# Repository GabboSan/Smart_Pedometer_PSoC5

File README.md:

# AY2022 I Project-1

Smart Pedometer project developed in a MSc Course of Politecnico di Milano:
Authors: 
1. Santicchi Gabriele
2. d'Arenzo Daniele 
3. Santini Matteo

In this work a PSoC CY8C5888LTI-LP097 communicates by I2C protocol with MPU9250, SSD1306, 24LC512 and by UART protocol with HC-06 Bluetooth.\
A PyQt5 GUI has been developed to upload sessions and set user credential.

## Aim of this Work

1. Implement a pedometer algorithm capable to identify and count steps online;
2. Exploit the over-threshold events interrupt of the MPU9250 to automatically wake up the device from sleep; go to sleep mode when no motion is detected for 1 minute;
3. Display in the GUI some statistics: total number of steps, average cadence, total activity time and the session path with respect to the origin (i.e. first 'step' detected);
4. Log the statistics of each session (i.e., of every walk detected) in the internal EEPROM of the PSoC;
5. Minimization of power consumption, by using powersaving functionalities of the PSoC (e.g., Alternate mode) as well as turining off external peripherals when not in use;
6. When connected via USB to the computer, the device can accept a data request and display/send the data stored into the EEPROM.

## MPU9250 and AHRS filtering

To keep track of the direction of the walk, the AHRS filter has been implemented to get a Roll-Pitch-Yaw estimate. As the filter needs the magnetometer measurements, the AK8963 is enabled and set as Slave on the I2C bus.
Each 2 seconds the pedometer algorithm compute the X and Y direction of the walk, by considering the RPY orientation of the device.
The two directions are saved as 16 bit and then saved into the cell of the EEPROM . Path is reconstructed by the PC through this relative coordinates system.

## EEPROM Session Data Structure

When no motion has been detected for 1 minute, the Wake-On-Motion (WOM) interrupt is enabled and session data are saved in the EEPROM with the following structure.\
**RESERVED CELL REGISTERS:**
* 0: Height;
* 1: UserID;
* 2: SessionID;
* 3-4: lastAddressEEPROM: to avoid data overwriting;

**CELL REGISTERS:**

From 24LC512 Datasheet, Read and Write max. operation number is limited to a Page size, which consist of 128 bytes. The Packets to be sent to the PC are structured as:

* UserID, SessionID, HEADER (0xFE,0xFF);
* dataXY: sequence of X and Y relative coordinates (in 16 bits) computed each 2 seconds;
* Number of Steps, TAIL (0xFF,0xFF);

## SSD1306 Display

The SSD1306 communicates by I2C with the Master. It displays the total step counter and the current speed (in cm/s) each 2 seconds. When the device enters in Sleep mode, the display is turned off.

## Final PCB ad Case

# Guide

## Device Guide

Device must be put parallel to the calf fibers in order to get meaningful information about the orientation. During a Session, the Step counter and the Current speed are updated each 2 seconds on the SSD1306 display.\
A session starts when the device is powered, and ends when no motion has been detected for more than 1 minute. Then, the session is saved into the memory and the device enter in sleep mode until detection of futher N steps.

## GUI Guide

While running the GUI, the Device must be connected either by USB or Bluetooth. Even if an automatic scan of ports is implemented, sometimes a manual selection of the COM is required.
To get meaningful information about the orientation, the calibration of the magnetometer is recommended (move the device along an eigth figure until the calibration is not finished).\
The GUI is organized in tabs:

* Sessions: see the statistics related to each session downloaded from the device;
* Live Viewer: see the Session path and the current 3D orientation of the device;
* Edit Profile: to create, delete and modify a user;
* Advanced Tool: monitor Accelerometer, Gyroscope and Magnetometer values in real-time.

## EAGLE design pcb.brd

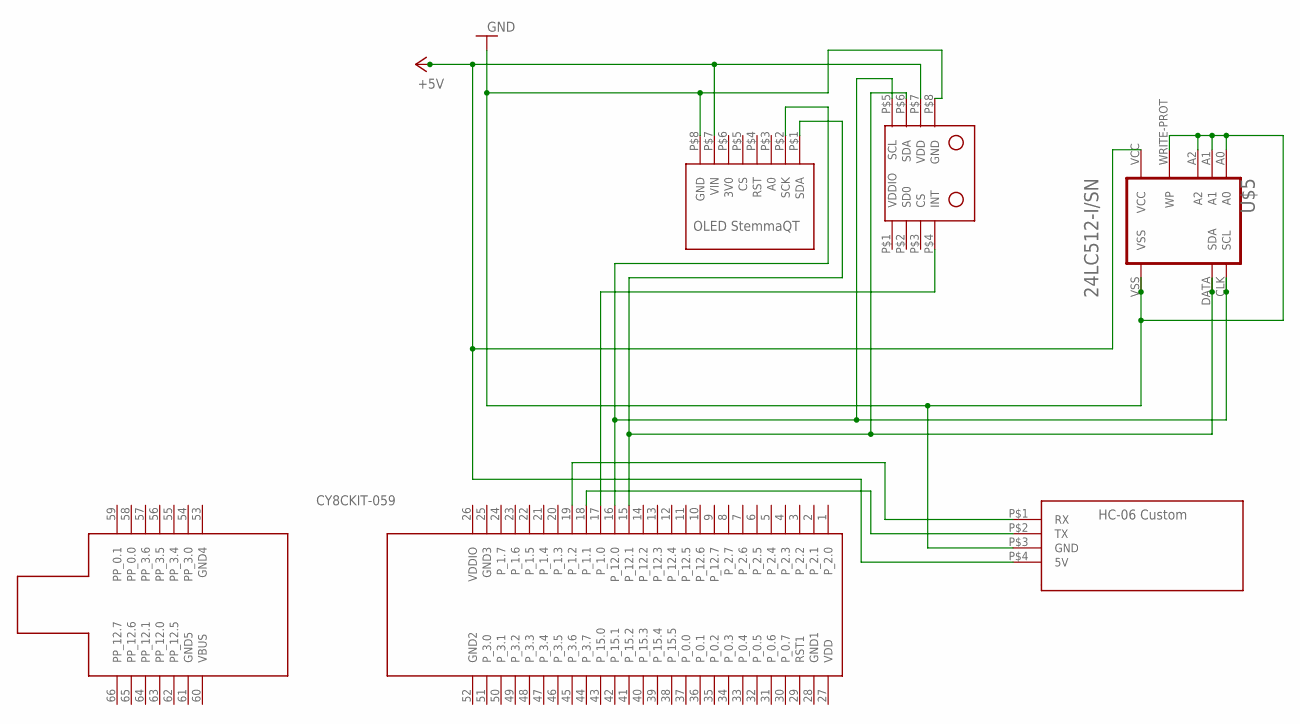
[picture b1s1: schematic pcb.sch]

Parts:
U$1: CY8CKIT-059
U$2: SSD1306_STEMMAQT_128X64; FTP_SSD1306_128X64_4PIN
U$3: HC-06_CUSTOM; FTP_HC-06_CUSTOM
U$4: MPU9250; FTP_MPU9650
U$5: 24LC512-I-CUSTOM

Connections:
+5V: U$2.P$7 (VIN), U$3.P$4 (5V), U$4.P$7 (VDD), U$5.VCC
GND: U$2.P$8 (GND), U$3.P$3 (GND), U$4.P$8 (GND), U$5.A0, U$5.A1, U$5.A2, U$5.VSS, U$5.WRITE-PROT (WP)
unnamed: U$1.19 (P_1.2), U$3.P$1 (RX)
unnamed: U$1.18 (P_1.1), U$3.P$2 (TX)
unnamed: U$1.16 (P_12.0), U$2.P$2 (SCK), U$4.P$5 (SCL), U$5.CLK (SCL)
unnamed: U$1.15 (P_12.1), U$2.P$1 (SDA), U$4.P$6 (SDA), U$5.DATA (SDA)
unnamed: U$1.17 (P_1.0), U$4.P$4 (INT)

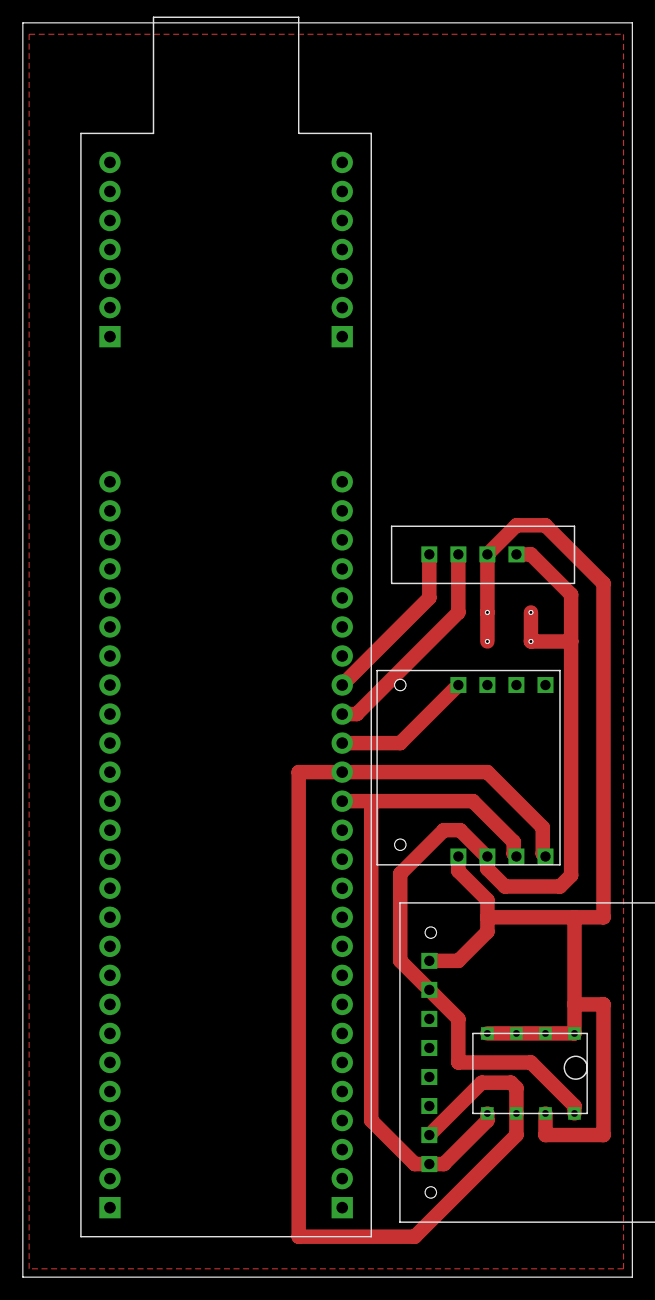
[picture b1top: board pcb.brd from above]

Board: 2 copper layers, 53.3 x 109.7 mm, 5 parts (0 on the bottom side), 7 nets.

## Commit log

2022-02-18 Final release
2022-02-18 add images
